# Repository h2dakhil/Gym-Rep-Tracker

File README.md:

# Fitness Rep Tracker 🏋️‍♂️

A **wrist-mounted STM32 wearable** that detects and classifies **4+ gym exercises** with real-time feedback.  
The project was built completely from scratch, including **custom 4-layer PCB design, embedded firmware, IMU motion sensing, and OLED feedback display.**

---

## 🚀 Features
- **Hardware**
  - Custom **4-layer PCB** designed in KiCad
  - MCU: **STM32F103**
  - IMU: **MPU-6050** (3-axis accelerometer + 3-axis gyroscope, I²C)
  - Display: **SSD1306 OLED** (128×64, I²C)
  - Power: **MCP73831 Li-ion charger**, 3.3 V LDO, battery-sense divider, USB-C input
  - Debug: **SWD header**, status LEDs

- **Firmware (C)**
  - Written in **C** using **PlatformIO** and STM32 HAL drivers
  - **IMU data acquisition** and calibration
  - **Rep detection algorithm** using peak prominence + refractory period filtering
  - Rolling buffer statistics & low-pass signal filters
  - State machine: boot → exercise selection → calibration → running
  - **OLED driver** for real-time rep count & status display
  - UART logging for debugging
  - Peripheral initialization with fallback & error handling

- **Testing & Debugging**
  - SMT soldered & validated using **DMM** and **oscilloscope**
  - Verified stable 3.3 V rail and signal nets

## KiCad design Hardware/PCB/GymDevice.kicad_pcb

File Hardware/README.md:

# Gym Rep Tracker Hardware

This directory contains the **hardware design files** for the Gym Rep Tracker, including schematics, PCB layouts, fabrication outputs, and backups.  
The hardware is built around the **STM32F103CBT6 microcontroller**, with supporting circuitry for the **MPU-6050 IMU**, **SSD1306 OLED**, battery charging, and power regulation.

---

## Directory Structure

- **Backups/**  
  Contains backup copies of hardware design files for recovery and version tracking.  

- **Fab/**  
  Fabrication-ready outputs, including Gerber files, drill files, and pick-and-place exports for PCB manufacturing.  

- **PCB/**  
  Source PCB design files (e.g., KiCad project files, layout, footprints).  
  - Includes board layout for the 4-layer stack-up (GND plane, power plane, signal layers).  

- **Schematic/**  
  Electrical schematics showing MCU, IMU, OLED, power management (MCP73831 Li-ion charger, LDO regulator), and supporting passives.  

- **README.md**  
  This file, describing the structure and usage of the hardware directory.  

---

## Usage

1. **View Schematics**  
   Open the files in the `Schematic/` folder using KiCad (recommended version noted in project files).  

2. **Edit PCB Layout**  
   Open the project in KiCad from the `PCB/` folder.  

3. **Generate Manufacturing Files**  
   Use KiCad’s *Plot* and *Fabrication Outputs* to regenerate Gerbers if changes are made.  
   Fabrication-ready files are already available in the `Fab/` folder.  

---

## Notes
- **Backups** are not guaranteed to be the latest version. Always check the active `PCB/` and `Schematic/` folders first.  
- Ensure fabrication files match the correct **4-layer stack-up** before sending to a manufacturer.  
- If modifying, confirm footprints and net connections pass ERC/DRC in KiCad before fabrication.

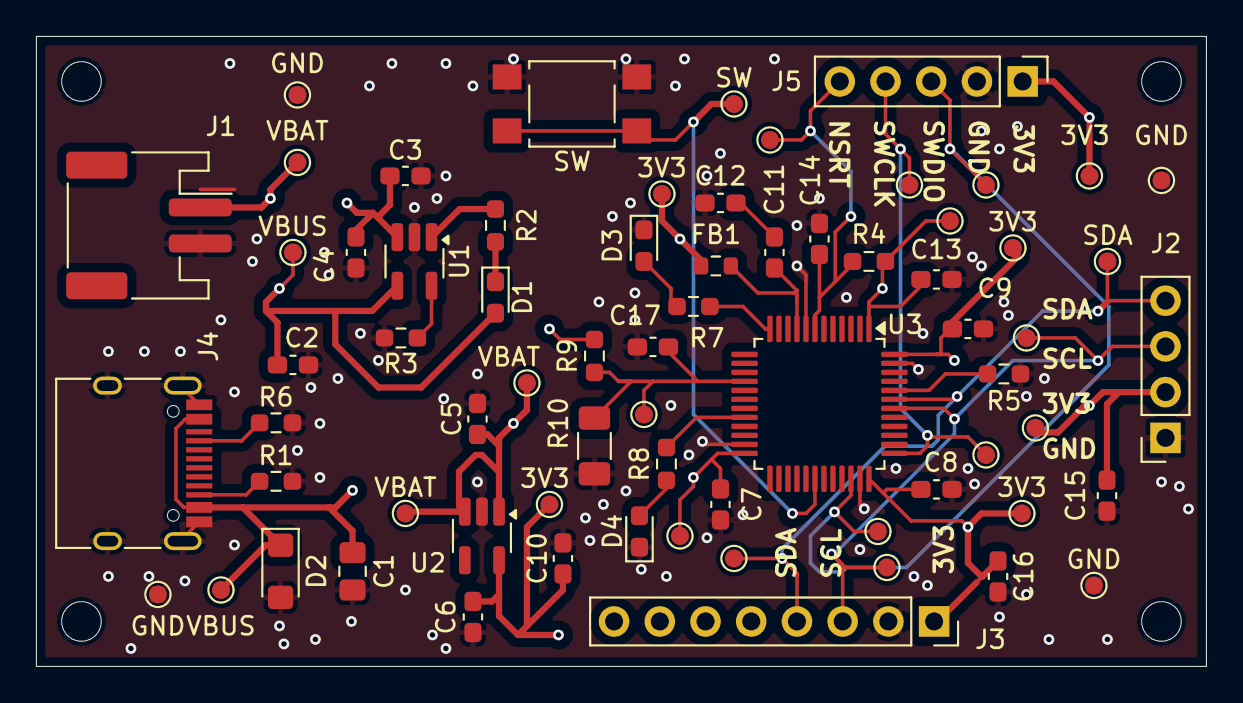
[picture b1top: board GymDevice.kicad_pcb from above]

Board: 4 copper layers, 65.0 x 35.0 mm, 57 parts (0 on the bottom side), 23 nets.

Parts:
3V3, 3V3#2, 3V3#3, 3V3#4, 3V3#5: TestPoint_Pad_D1.0mm
 VBAT: TestPoint_Pad_D1.0mm
C1: 10uF; C_0805_2012Metric_Pad1.18x1.45mm_HandSolder
C2, C3, C4, C10, C12: 4.7uF; C_0603_1608Metric_Pad1.08x0.95mm_HandSolder
C5, C6: 1uF; C_0603_1608Metric_Pad1.08x0.95mm_HandSolder
C7, C8, C9, C11, C13, C14, C15, C16, C17: 0.1uF; C_0603_1608Metric_Pad1.08x0.95mm_HandSolder
D1, D3, D4: LED; LED_0603_1608Metric_Pad1.05x0.95mm_HandSolder
D2: TVS; D_SMF
FB1: FerriteBead_Small; R_0603_1608Metric
GND: TestPoint_Pad_D1.0mm
GND#2, GND#3, GND#4: TestPoint_Pad_D1.0mm
J1: JST S2B-PH-SM4-TB(LF)(SN); JST_PH_S2B-PH-SM4-TB_1x02-1MP_P2.00mm_Horizontal
J2: SSD1306 I2C 128x32 OLED Module; PinSocket_1x04_P2.54mm_Vertical
J3: IMU Breakout Board; PinSocket_1x08_P2.54mm_Vertical
J4: USB_C_Receptacle_USB2.0_16P; USB_C_Receptacle_HRO_TYPE-C-31-M-12
J5: ST-Link; PinHeader_1x05_P2.54mm_Vertical
R1, R6: 5.1k; R_0603_1608Metric_Pad0.98x0.95mm_HandSolder
R2: 470; R_0603_1608Metric_Pad0.98x0.95mm_HandSolder
R3: 2k; R_0603_1608Metric_Pad0.98x0.95mm_HandSolder
R4, R5: 10k; R_0603_1608Metric_Pad0.98x0.95mm_HandSolder
R7, R8: 1k; R_0603_1608Metric_Pad0.98x0.95mm_HandSolder
R9: 100k; R_0603_1608Metric_Pad0.98x0.95mm_HandSolder
R10: 240k; R_1206_3216Metric_Pad1.30x1.75mm_HandSolder
SDA: TestPoint_Pad_D1.0mm
SW: TestPoint_Pad_D1.0mm
SW#2: SW_Push; SW_SPST_TL3305A
U1: MCP73831-2-OT; SOT-23-5_HandSoldering
U2: MIC5504-3.3YM5; SOT-23-5_HandSoldering
U3: STM32F103C8Tx; LQFP-48_7x7mm_P0.5mm
VBAT: TestPoint_Pad_D1.0mm
VBAT#2: TestPoint_Pad_D1.0mm
VBUS: TestPoint_Pad_D1.0mm
VBUS#2: TestPoint_Pad_D1.0mm

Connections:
/3V3: 3V3.1, 3V3#2.1, 3V3#3.1, 3V3#4.1, 3V3#5.1, C6.1, C7.1, C8.2, C9.1, C10.1, C13.2, C15.1, C16.1, FB1.2, J2.2, J3.1, J5.1, R4.1, U2.5 (VOUT), U3.1 (VBAT), U3.24 (VDD), U3.36 (VDD), U3.48 (VDD)
/NSRT: C14.1, J5.5, R4.2, U3.7 (NRST)
/SCL: J2.3, J3.3, U3.42 (PB6)
/SDA: J2.4, J3.4, SDA.1, U3.43 (PB7)
/SWCLK: J5.4, U3.37 (PA14)
/SWDIO: J5.3, U3.34 (PA13)
/VBAT: VBAT.1, C3.1, C4.1, C5.1, J1.1, R9.1, U1.3 (V_{BAT}), U2.1 (VIN), U2.3 (EN), VBAT.1, VBAT#2.1
/VBAT_SENSE: C17.1, R9.2, R10.1, U3.16 (PA6)
/VBUS: C1.2, C2.2, D1.2 (A), D2.1 (K), J4.A4 (VBUS), J4.A9 (VBUS), J4.B4 (VBUS), J4.B9 (VBUS), U1.4 (V_{DD}), VBUS.1, VBUS#2.1
GND: C1.1, C2.1, C3.2, C4.2, C5.2, C6.2, C7.2, C8.1, C9.2, C10.2, C12.2, C13.1, C14.2, C15.2, C16.2, C17.2, D2.2 (A), D3.1 (K), D4.1 (K), GND.1, GND#2.1, GND#3.1, GND#4.1, J1.2, J2.1, J3.2, J4.A1 (GND), J4.A12 (GND), J4.B1 (GND), J4.B12 (GND), J4.S1 (SHIELD), J5.2, R1.2, R3.2, R5.1, R6.2, R10.2, SW#2.2, U1.2 (V_{SS}), U2.2 (GND), U3.8 (VSSA), U3.23 (VSS), U3.35 (VSS), U3.47 (VSS)
unnamed: C11.2, C12.1
unnamed: D1.1 (K), R2.1
unnamed: D3.2 (A), R7.2
unnamed: D4.2 (A), R8.2
unnamed: J4.A5 (CC1), R6.1
unnamed: J4.B5 (CC2), R1.1
unnamed: R3.1, U1.5 (PROG)
unnamed: R2.2, U1.1 (STAT)
unnamed: R5.2, U3.44 (BOOT0)
unnamed: R7.1, U3.12 (PA2)
unnamed: SW#2.1, U3.30 (PA9)
unnamed: R8.1, U3.20 (PB2)
unnamed: C11.1, FB1.1, U3.9 (VDDA)

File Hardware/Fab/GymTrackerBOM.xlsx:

BOM: Gym Rep Tracker Device
Haya Dakhil
Designator | Description | Quantity | Value | Package/ Footprint |  | Manufacturer Part Number (MPN) |  |  | Supplier | Supplier part number |  | Link
J1 | Battery Connector | 1 |  | JST_PH_S2B-PH-SM4-TB_1x02-1MP_P2.00mm_Horizontal |  | S2B-PH-SM4-TB(LF)(SN) |  |  | LCSC | C295747 |  | https://www.lcsc.com/product-detail/C295747.html?s_z=n_JST%2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
J2 | Female OLED Conn | 1 |  | Connector_PinSocket_2.54mm:PinSocket_1x04_P2.54mm_Vertical |  | BOOMELE(Boom Precision Elec) 2.54-1*4P |  |  | LCSC | C2718488 |  | https://www.lcsc.com/product-detail/C2718488.html
DNP | Male OLED Pin | 1 |  |  |  | B-2100S04P-A110 |  |  | LCSC | C124378 |  | https://www.lcsc.com/product-detail/C124378.html?s_z=n_C124378
DNP | OLED Display | 1 |  |  |  | HS91L02W2C01 |  |  | LCSC | C5248081 |  | https://www.lcsc.com/product-detail/C5248081.html?s_z=n_C5248081
DNP | IMU Breakout Board | 1 |  |  |  |  |  |  | Amazon |  |  | https://www.amazon.ca/Acceleration-Sensors-Accelerometer-Thr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
J3 | Female IMU Connector | 1 |  | Connector_PinSocket_2.54mm:PinSocket_1x08_P2.54mm_Vertical |  | 2.54-1*8P |  |  | LCSC | C27438 |  | https://www.lcsc.com/product-detail/C27438.html?s_z=n_1x8%25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
J4 | USBC Connector | 1 |  | Connector_USB:USB_C_Receptacle_HRO_TYPE-C-31-M-12 |  | TYPE-C-31-M-12 |  |  | LCSC | C165948 |  | https://www.lcsc.com/product-detail/C165948.html
J5 | SWD Header | 1 |  | Connector_PinHeader_2.54mm:PinHeader_1x05_P2.54mm_Vertical |  | PH2.54-1X5P-H25 |  |  | LCSC | C42431835 |  | https://www.lcsc.com/product-detail/C42431835.html?s_z=n_1x5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
DNP | SWD Linker | 1 |  |  |  |  |  |  |  |  |  | https://www.amazon.ca/DAOKAI-Downloader-Programmer-STM8STM32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
DNP | Adapter USB-A to C | 1 |  |  |  |  |  |  |  |  |  | https://www.amazon.ca/Female-Adapter-Charger-Airpods-Samsung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
DNP | Battery | 1 |  |  |  |  |  |  |  |  |  | https://www.amazon.ca/FITHOOD-Rechargeable-Connector-Househo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
U1 | PMIC | 1 |  | Package_TO_SOT_SMD:SOT-23-5 MIC5504-3.3YM5-TR |  | MCP73831T-2ACI/OT |  |  | LCSC | C424093 |  | https://www.lcsc.com/product-detail/C424093.html?s_z=n_C424093
U2 | LDO | 1 |  | Package_TO_SOT_SMD:SOT-23-5 |  | MIC5504-3.3YM5-TR |  |  | LCSC | C88419 |  | https://www.lcsc.com/product-detail/C88419.html?s_z=n_C88419
U3 | STM32 MCU | 1 |  | Package_QFP:LQFP-48_7x7mm_P0.5mm |  | STM32F103C8T6 |  |  | LCSC | C8734 |  | https://www.lcsc.com/product-detail/C8734.html?s_z=n_STM32F103C8T6
D1, D3 | Green LED | 2 |  | LED_SMD:LED_0603_1608Metric_Pad1.05x0.95mm_HandSolder |  | A-SP192DGHC-C01-4T |  |  | LCSC | C19171301 |  | https://www.lcsc.com/product-detail/C19171301.html?s_z=n_gre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
D2 | TVS Diode | 1 |  | Diode_SMD:D_SMF |  | SMF5.0A |  |  | LCSC | C151296 |  | https://www.lcsc.com/product-detail/C151296.html?s_z=n_SMF5.0A
D4 | Yellow LED | 1 |  | LED_SMD:LED_0603_1608Metric_Pad1.05x0.95mm_HandSolder |  | XL-1608UYC-06 |  |  | LCSC | C965802 |  | https://www.lcsc.com/product-detail/C965802.html?s_z=n_yellow%20led
FB1 | Ferrite Bead | 1 |  | Resistor_SMD:R_0603_1608Metric |  | BLM18PG121SN1D |  |  | LCSC | C14709 |  | https://www.lcsc.com/product-detail/C14709.html?s_z=n_ferrit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
R1, R6 |  | 2 | 5.1k | Resistor_SMD:R_0603_1608Metric |  | RC0603FR-075K1L |  |  | LCSC | C105580 |  | https://www.lcsc.com/product-detail/C105580.html?s_z=n_5.1k%2520r
R2 |  | 1 | 470 | Resistor_SMD:R_0603_1608Metric |  | RC0603FR-07470RL |  |  | LCSC | C114669 |  | https://www.lcsc.com/product-detail/C114669.html?s_z=n_470%2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
R3 |  | 1 | 2.0k | Resistor_SMD:R_0603_1608Metric |  | FRC0603J202 TS |  |  | LCSC | C2907137 |  | https://www.lcsc.com/product-detail/C2907137.html?s_z=n_2k%2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
R4, R5 |  | 2 | 10k | Resistor_SMD:R_0603_1608Metric |  | RC0603FR-0710KL |  |  | LCSC | C98220 |  | https://www.lcsc.com/product-detail/C98220.html?s_z=n_10k%25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
R7, R8 |  | 2 | 1k | Resistor_SMD:R_0603_1608Metric |  | RC0603FR-071KL |  |  | LCSC | C22548 |  | https://www.lcsc.com/product-detail/C22548.html?s_z=n_1kohm%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
R9 |  | 1 | 100k | Resistor_SMD:R_0603_1608Metric |  | RC0603FR-07100KL |  |  | LCSC | C14675 |  | https://www.lcsc.com/product-detail/C14675.html?s_z=n_100koh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
R10 |  | 1 | 240k | Resistor_SMD:R_1206_3216Metric |  | FRC1206F2403TS |  |  | LCSC | C2907378 |  | https://www.lcsc.com/product-detail/C2907378.html?s_z=n_240k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
C1 |  | 1 | 10uF | Capacitor_SMD:C_0805_2012Metric_Pad1.18x1.45mm_HandSolder |  | 0805X5R106K500NT |  |  | LCSC | C48579582 |  | https://www.lcsc.com/product-detail/C48579582.html?s_z=n_10u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
C2, C3, C4, C10, C12 |  | 5 | 4.7uF | Capacitor_SMD:C_0603_1608Metric |  | CC0603KRX5R6BB475 |  |  | LCSC | C109456 |  | https://www.lcsc.com/product-detail/C109456.html?s_z=n_4.7uf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
C5, C6 |  | 2 | 1uF | Capacitor_SMD:C_0603_1608Metric_Pad1.08x0.95mm_HandSolder |  | CC0603KRX7R9BB105 |  |  | LCSC | C559769 |  | https://www.lcsc.com/product-detail/C559769.html?s_z=n_1uF%2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
C7, C8, C9, C11, C13, C14, C15, C16, C17 |  | 9 | 0.1uF | Capacitor_SMD:C_0603_1608Metric_Pad1.08x0.95mm_HandSolder |  |  |  |  | LCSC | C14663 |  | https://www.lcsc.com/product-detail/C14663.html?s_z=n_0.1uF%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
SW1 | Start Button | 1 |  | Button_Switch_SMD:SW_SPST_TL3305A |  | TS-1187A-C-E-B |  |  | LCSC | C318887 |  | https://www.lcsc.com/product-detail/C318887.html
 | Helping hands |  |  |  |  |  |  |  |  |  |  | https://www.amazon.ca/STANZ-Magnifying-Selected-Soldering-El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
 | Flux |  |  |  |  |  |  |  |  |  |  | https://www.amazon.ca/TOWOT-Rosin-Solder-Paste-Soldering/dp/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
 | Wick |  |  |  |  |  |  |  |  |  |  | https://www.amazon.ca/Solder-TOWOT-Desoldering-Wicks-SW-2530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

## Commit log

2025-07-18 Create hardware
2025-07-18 Update hardware
2025-07-18 Create firmware
2025-07-18 Create mechanical
2025-07-18 Create python-logger
2025-07-18 Create images
2025-07-18 Create LICENSE
2025-09-06 Add firmware under /Firmware
2025-09-17 Inputted all project files
2025-09-17 README updated
2025-09-17 added README
